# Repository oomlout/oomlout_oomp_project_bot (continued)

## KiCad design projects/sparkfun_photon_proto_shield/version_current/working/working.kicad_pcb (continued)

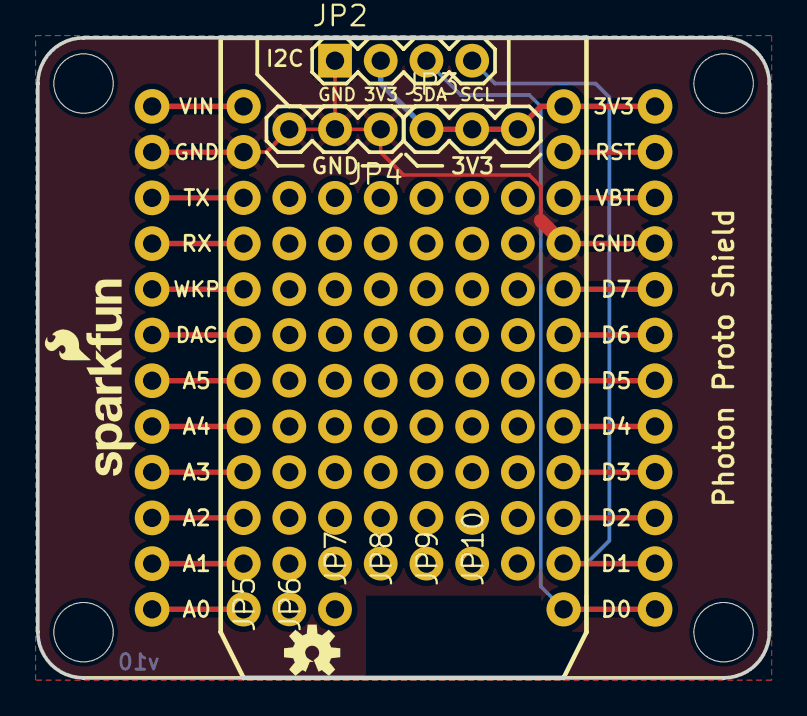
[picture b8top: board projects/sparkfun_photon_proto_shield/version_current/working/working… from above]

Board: 2 copper layers, 40.6 x 35.6 mm, 14 parts (1 on the bottom side), 23 nets.

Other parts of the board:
LOGO3: SFE_LOGO_NAME_FLAME.1_INCH; SFE_LOGO_NAME_FLAME_.1
